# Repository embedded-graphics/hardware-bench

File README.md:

# Embedded graphics hardware test bench

Requires KiCAD 6.x.

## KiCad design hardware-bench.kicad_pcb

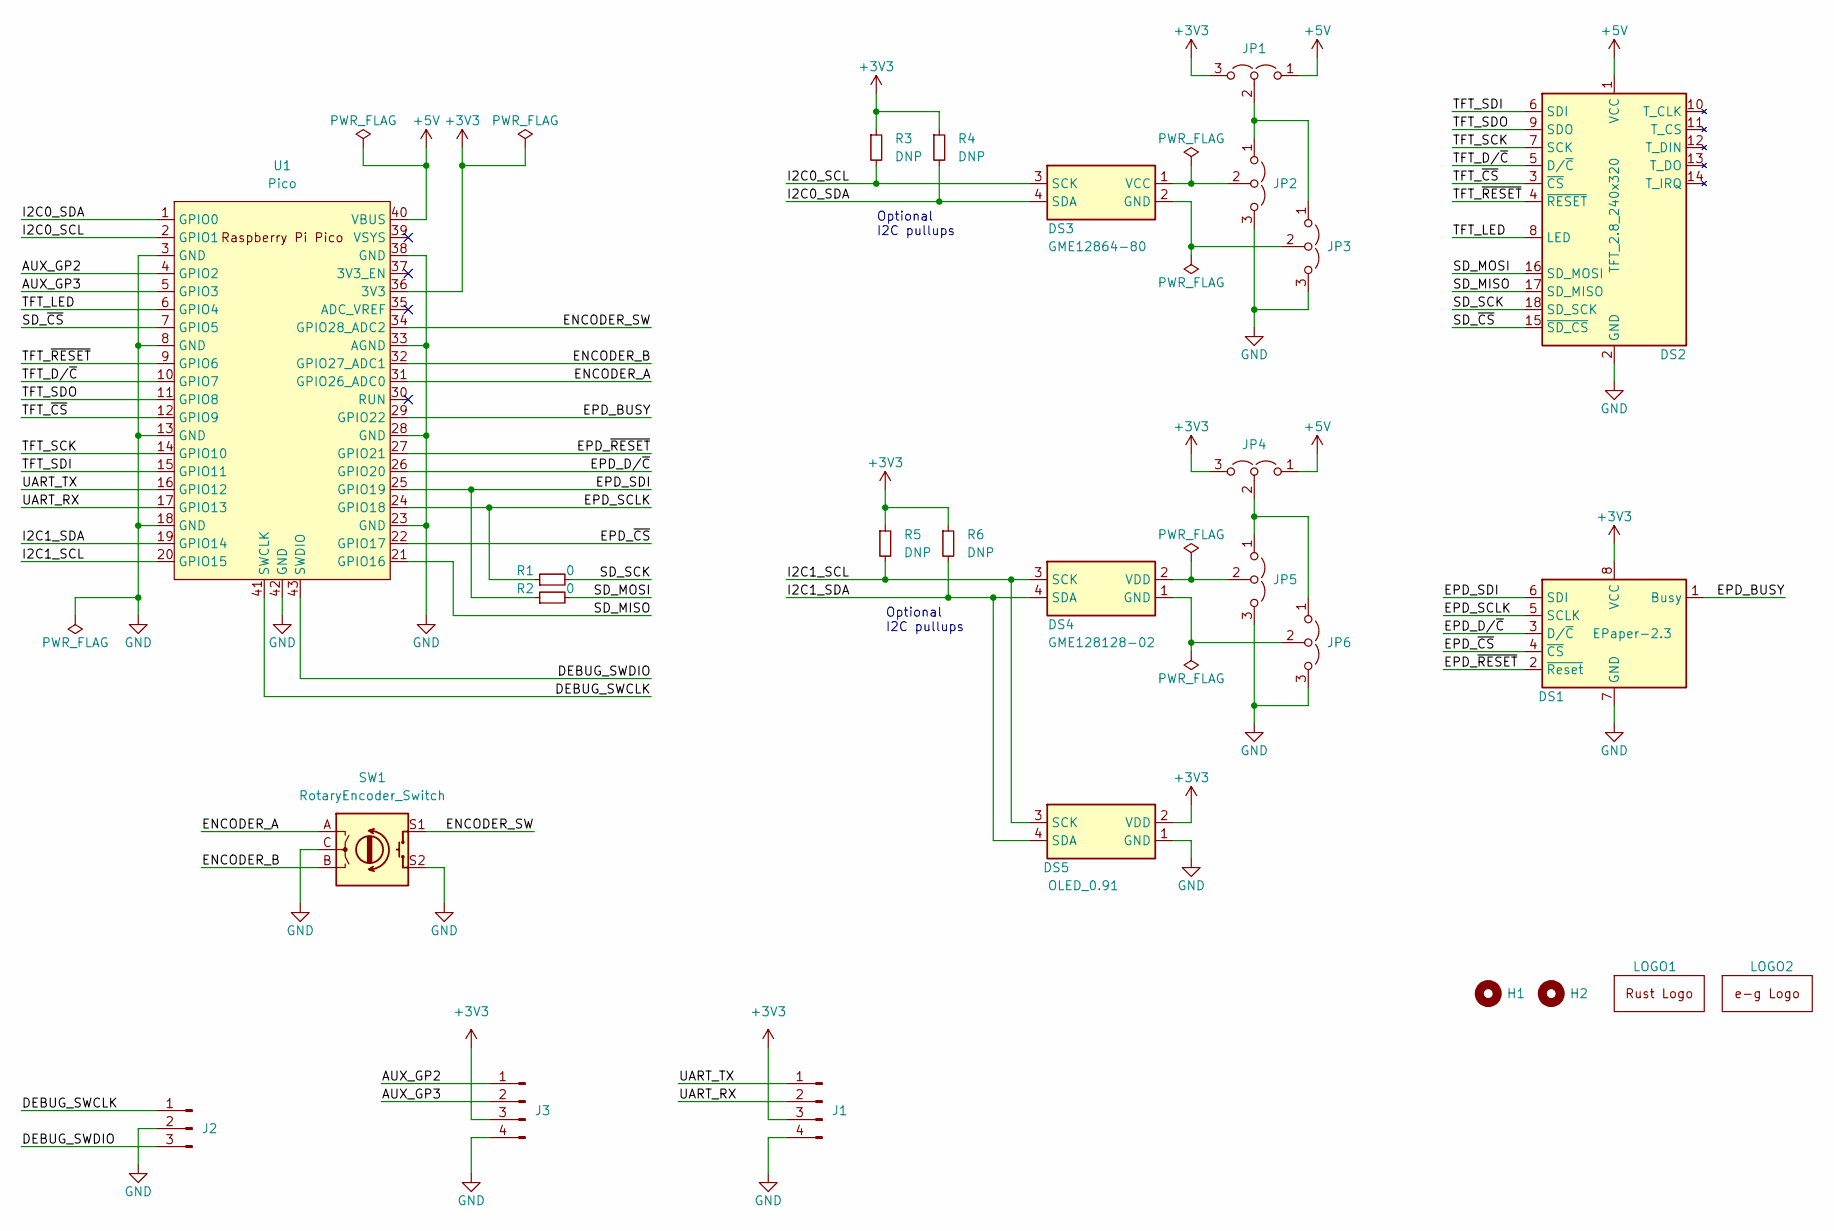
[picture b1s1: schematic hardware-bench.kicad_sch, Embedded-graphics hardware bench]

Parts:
DS1: EPaper-2.3; EPaper-2.13
DS2: TFT_2.8_240x320
DS3: GME12864-80
DS4: GME128128-02
DS5: OLED_0.91
H1, H2: MountingHole; MountingHole_3.2mm_M3
J1, J3: Conn_01x04_Male; PinHeader_1x04_P2.54mm_Horizontal_Flipped
J2: Conn_01x03_Male; PinHeader_1x03_P2.54mm_Horizontal_Flipped
JP1, JP2, JP3, JP4, JP5, JP6: Jumper_3_Open; PinHeader_1x03_P2.54mm_Vertical
LOGO1: Logo_Rust
LOGO2: Logo_E_G
R1, R2: 0; R_0603_1608Metric
R3, R4, R5, R6: DNP; R_0603_1608Metric
SW1: RotaryEncoder_Switch; RotaryEncoder_Alps_EC12E-Switch_Vertical_H20mm_CircularMoun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
U1: Pico; RPi_Pico_SMD

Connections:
+3V3: DS1.8 (VCC), DS5.2 (VDD), J1.3, J3.3, JP1.3 (B), JP4.3 (B), R3.1, R4.1, R5.1, R6.1, U1.36 (3V3)
+5V: DS2.1 (VCC), JP1.1 (A), JP4.1 (A), U1.40 (VBUS)
/AUX_GP2: J3.1, U1.4 (GPIO2)
/AUX_GP3: J3.2, U1.5 (GPIO3)
/DEBUG_SWCLK: J2.1, U1.41 (SWCLK)
/DEBUG_SWDIO: J2.3, U1.43 (SWDIO)
/ENCODER_A: SW1.A, U1.31 (GPIO26_ADC0)
/ENCODER_B: SW1.B, U1.32 (GPIO27_ADC1)
/ENCODER_SW: SW1.S1, U1.34 (GPIO28_ADC2)
/EPD_BUSY: DS1.1 (Busy), U1.29 (GPIO22)
/EPD_D/~C: DS1.3 (D/~C), U1.26 (GPIO20)
/EPD_SCLK: DS1.5 (SCLK), R1.1, U1.24 (GPIO18)
/EPD_SDI: DS1.6 (SDI), R2.1, U1.25 (GPIO19)
/EPD_~CS: DS1.4 (~CS), U1.22 (GPIO17)
/EPD_~RESET: DS1.2 (~Reset), U1.27 (GPIO21)
/I2C0_SCL: DS3.3 (SCK), R3.2, U1.2 (GPIO1)
/I2C0_SDA: DS3.4 (SDA), R4.2, U1.1 (GPIO0)
/I2C1_SCL: DS4.3 (SCK), DS5.3 (SCK), R5.2, U1.20 (GPIO15)
/I2C1_SDA: DS4.4 (SDA), DS5.4 (SDA), R6.2, U1.19 (GPIO14)
/SD_MISO: DS2.17 (SD_MISO), U1.21 (GPIO16)
/SD_MOSI: DS2.16 (SD_MOSI), R2.2
/SD_SCK: DS2.18 (SD_SCK), R1.2
/SD_~CS: DS2.15 (~SD_CS), U1.7 (GPIO5)
/TFT_D/~C: DS2.5 (D/~C), U1.10 (GPIO7)
/TFT_LED: DS2.8 (LED), U1.6 (GPIO4)
/TFT_SCK: DS2.7 (SCK), U1.14 (GPIO10)
/TFT_SDI: DS2.6 (SDI), U1.15 (GPIO11)
/TFT_SDO: DS2.9 (SDO), U1.11 (GPIO8)
/TFT_~CS: DS2.3 (~CS), U1.12 (GPIO9)
/TFT_~RESET: DS2.4 (~RESET), U1.9 (GPIO6)
/UART_RX: J1.2, U1.17 (GPIO13)
/UART_TX: J1.1, U1.16 (GPIO12)
GND: DS1.7 (GND), DS2.2 (GND), DS5.1 (GND), J1.4, J2.2, J3.4, JP2.3 (B), JP3.3 (B), JP5.3 (B), JP6.3 (B), SW1.C, SW1.S2, U1.3 (GND), U1.8 (GND), U1.13 (GND), U1.18 (GND), U1.23 (GND), U1.28 (GND), U1.33 (AGND), U1.38 (GND), U1.42 (GND)
unnamed: DS3.1 (VCC), JP2.2 (C)
unnamed: DS3.2 (GND), JP3.2 (C)
unnamed: DS4.1 (GND), JP6.2 (C)
unnamed: DS4.2 (VDD), JP5.2 (C)
unnamed: JP1.2 (C), JP2.1 (A), JP3.1 (A)
unnamed: JP4.2 (C), JP5.1 (A), JP6.1 (A)

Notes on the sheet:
Optional I2C pullups

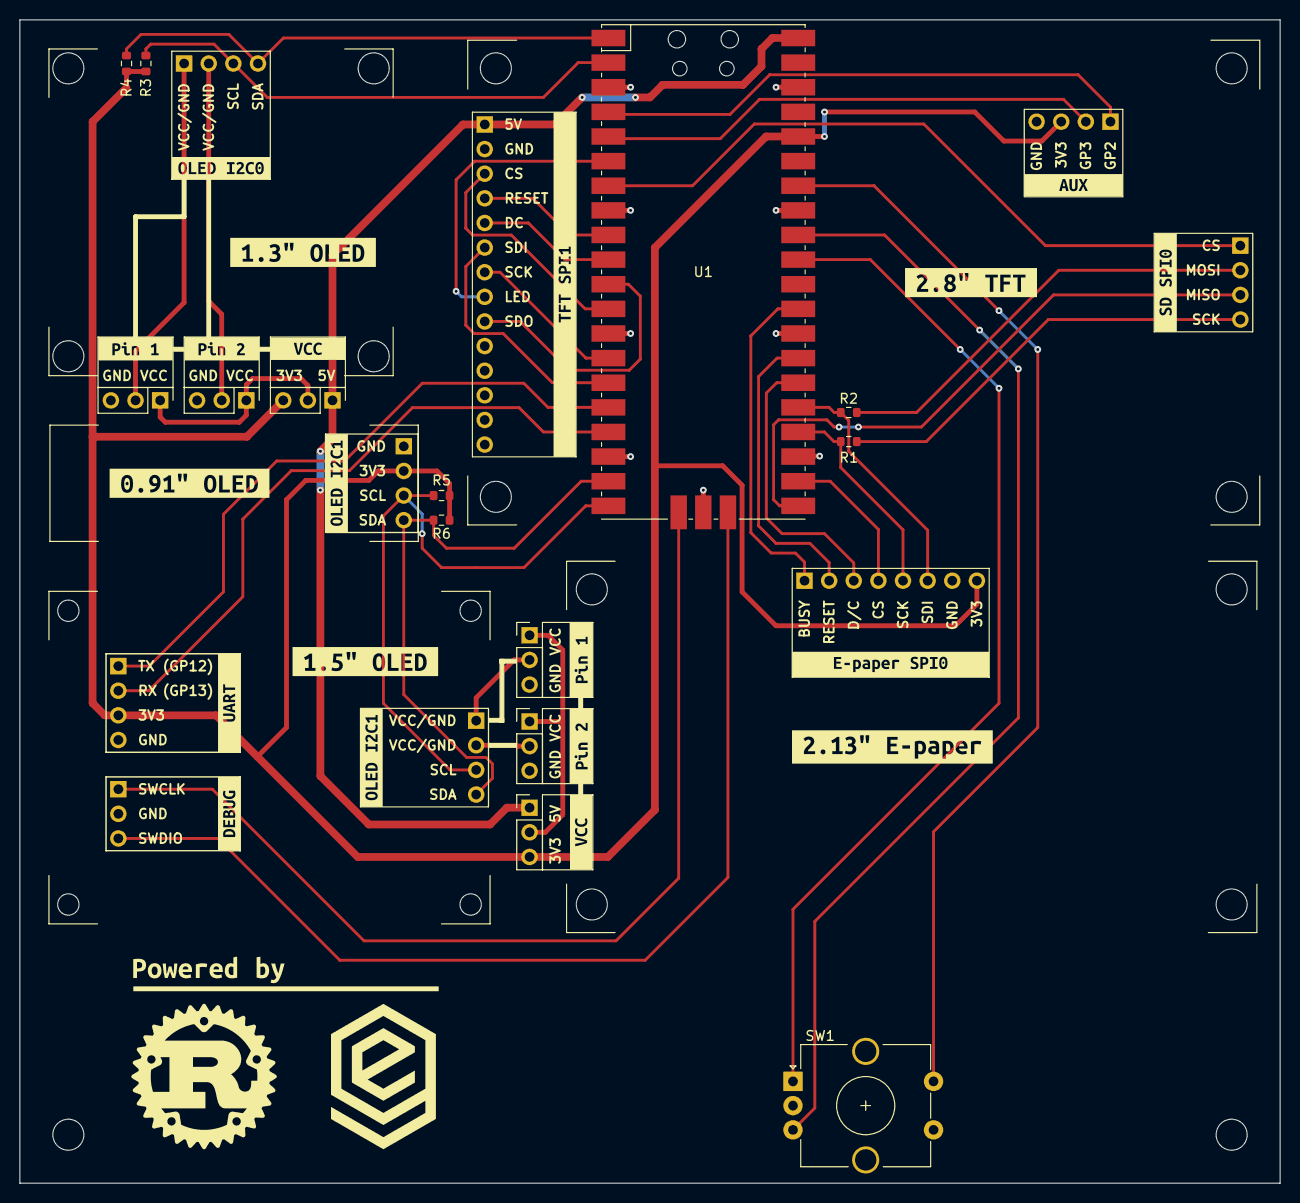
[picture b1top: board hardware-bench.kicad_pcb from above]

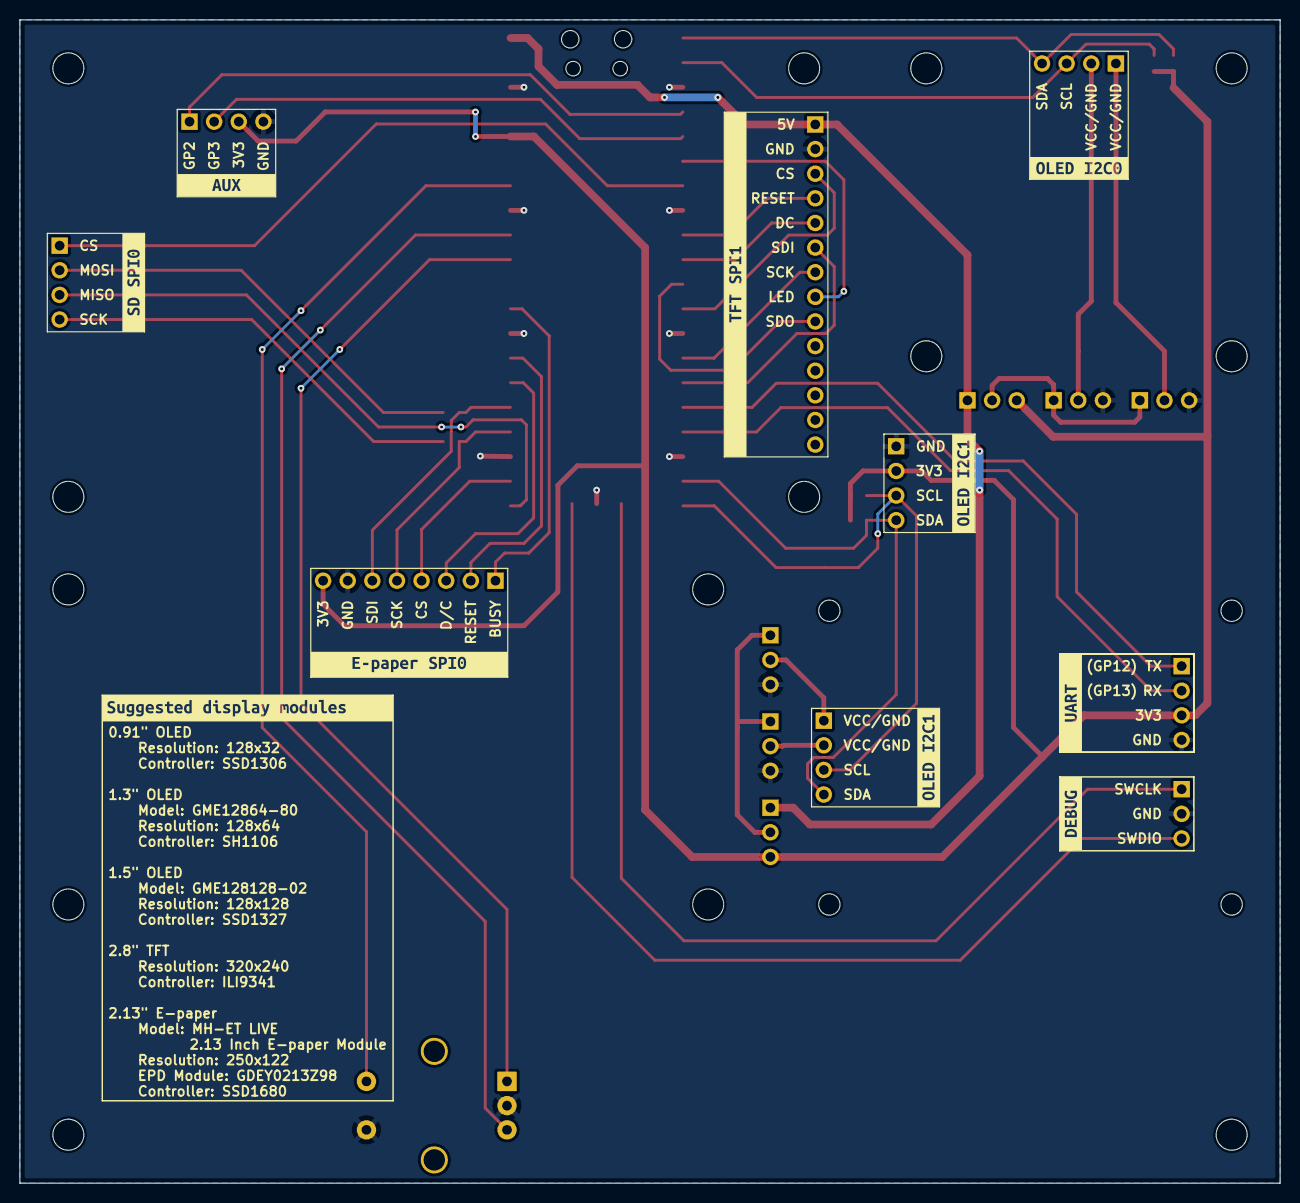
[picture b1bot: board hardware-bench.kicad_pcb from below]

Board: 2 copper layers, 130.0 x 120.0 mm, 57 parts (10 on the bottom side), 39 nets.

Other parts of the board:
kibuzzard-635BBA92: G***; kibuzzard-635BBA92
kibuzzard-636E8B55, kibuzzard-636E8B55#2: G***; kibuzzard-636E8B55
kibuzzard-636E8BC3, kibuzzard-636E8BC3#2: G***; kibuzzard-636E8BC3
kibuzzard-636E8C97, kibuzzard-636E8C97#2: G***; kibuzzard-636E8C97
kibuzzard-636E8D2A, kibuzzard-636E8D2A#2: G***; kibuzzard-636E8D2A
kibuzzard-636E8D77, kibuzzard-636E8D77#2: G***; kibuzzard-636E8D77
kibuzzard-636E8E76, kibuzzard-636E8E76#2: G***; kibuzzard-636E8E76
kibuzzard-636E8FDA, kibuzzard-636E8FDA#2: G***; kibuzzard-636E8FDA
kibuzzard-636E96FA: G***; kibuzzard-636E96FA
kibuzzard-636E891A, kibuzzard-636E891A#2, kibuzzard-636E891A#3, kibuzzard-636E891A#4: G***; kibuzzard-636E891A
kibuzzard-636E971C: G***; kibuzzard-636E971C
kibuzzard-636E9700: G***; kibuzzard-636E9700
kibuzzard-636E9707: G***; kibuzzard-636E9707
kibuzzard-636E9711: G***; kibuzzard-636E9711
kibuzzard-636E9726: G***; kibuzzard-636E9726
kibuzzard-636EACB9: G***; kibuzzard-636EACB9
kibuzzard-636EB72B: G***; kibuzzard-636EB72B
kibuzzard-636EB73F: G***; kibuzzard-636EB73F
kibuzzard-636EB715: G***; kibuzzard-636EB715
kibuzzard-636EB722: G***; kibuzzard-636EB722
kibuzzard-636EB734: G***; kibuzzard-636EB734

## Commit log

2022-04-20 Initial commit with SSD1306 and ILI9341
2022-04-20 Quick readme
2022-11-12 Raspberry PI Pico hardware bench
2022-11-12 Raspberry PI Pico hardware bench (#2)
